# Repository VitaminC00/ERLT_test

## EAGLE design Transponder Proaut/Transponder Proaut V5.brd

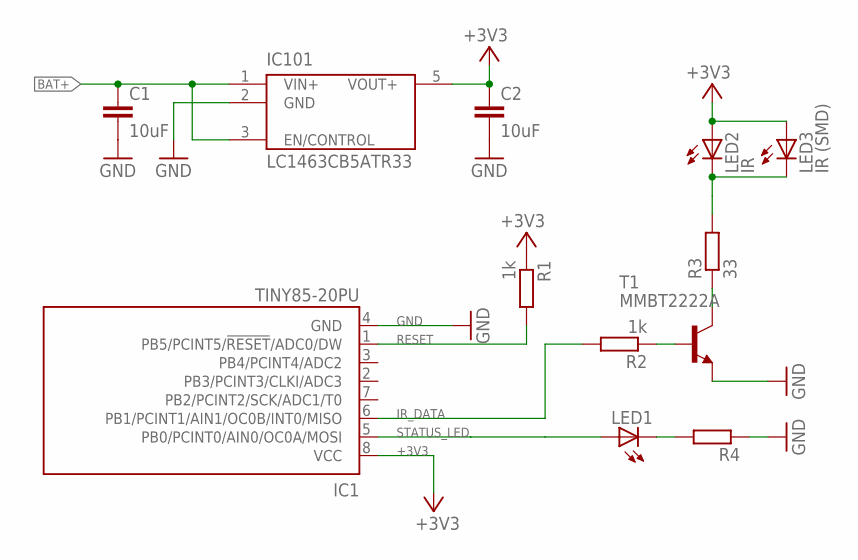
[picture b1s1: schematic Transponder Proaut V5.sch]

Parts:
C1, C2: 10uF; C0805K
IC1: TINY85-20PU; 8S2
IC101: LC1463CB5ATR33; SOT23-5
LED1: LEDCHIPLED_0805; CHIPLED_0805
LED2: IR; LED5MM
LED3: IR (SMD); CHIPLED_0805
R1, R2: 1k; R0805@1
R3: 33; R0805@1
R4: R-EU_R0805; R0805@1
T1: MMBT2222A; SOT23-BEC

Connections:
+3V3: C2.1, IC1.8 (VCC), IC101.5 (VOUT+), LED2.A, LED3.A, R1.1
BAT+: C1.1, IC101.1 (VIN+), IC101.3 (EN/CONTROL)
GND: C1.2, C2.2, IC1.4 (GND), IC101.2 (GND), R4.1, T1.E
IR_DATA: IC1.6 (PB1/PCINT1/AIN1/OC0B/INT0/MISO), R2.2
unnamed: LED2.K (C), LED3.C, R3.2
unnamed: R3.1, T1.C
unnamed: R2.1, T1.B
unnamed: LED1.C, R4.2
RESET: IC1.1 (PB5/PCINT5/!RESET!/ADC0/DW), R1.2
STATUS_LED: IC1.5 (PB0/PCINT0/AIN0/OC0A/MOSI), LED1.A

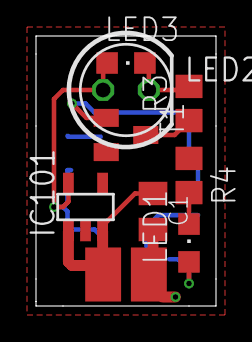
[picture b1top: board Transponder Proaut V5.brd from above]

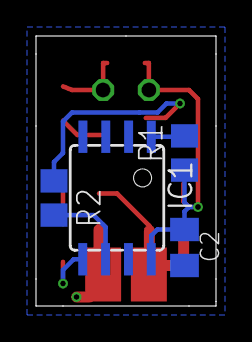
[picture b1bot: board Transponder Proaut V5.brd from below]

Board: 2 copper layers, 10.0 x 15.0 mm, 12 parts (4 on the bottom side), 10 nets.

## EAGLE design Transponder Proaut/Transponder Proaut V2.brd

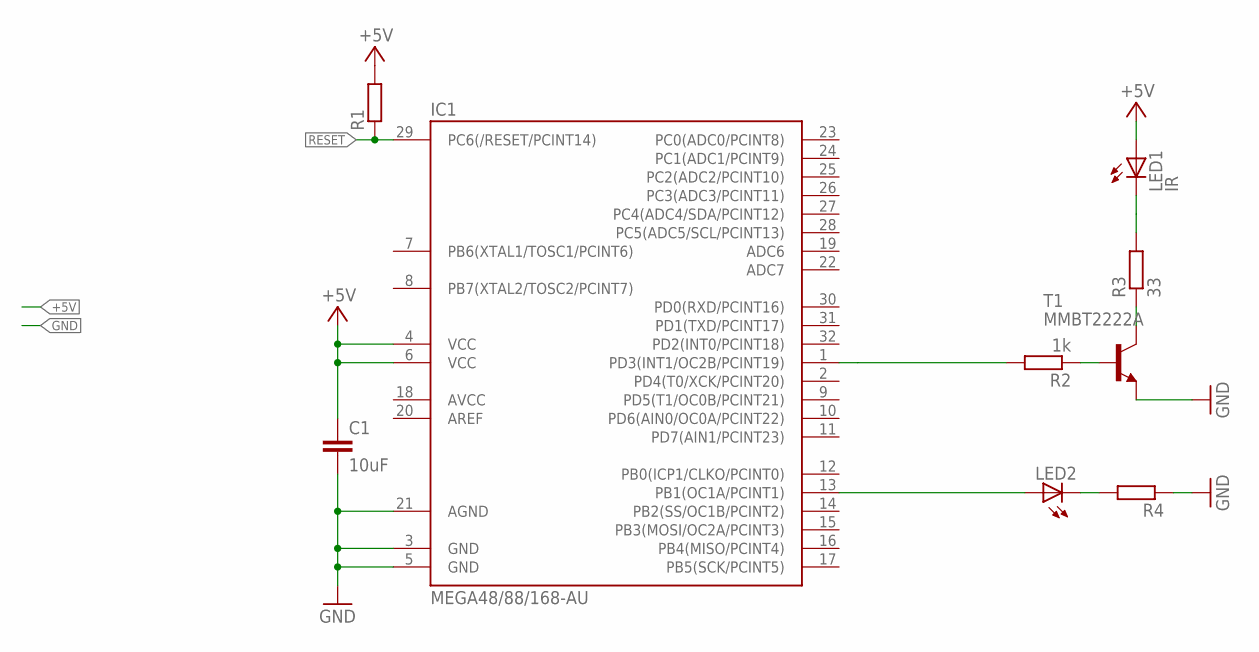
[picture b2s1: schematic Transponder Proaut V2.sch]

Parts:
C1: 10uF; C0805
IC1: MEGA48/88/168-AU; TQFP32-08
LED1: IR; LED5MM
LED2: LEDSML1206; SML1206
R1, R4: R-EU_R0805; R0805@1
R2: 1k; R0805@1
R3: 33; R0805@1
T1: MMBT2222A; SOT23-BEC

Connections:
+5V: C1.1, IC1.4 (VCC), IC1.6 (VCC), LED1.A, R1.2
GND: C1.2, IC1.3 (GND), IC1.5 (GND), IC1.21 (AGND), R4.1, T1.E
IR_LED: IC1.1 (PD3(INT1/OC2B/PCINT19)), R2.2
unnamed: LED1.K (C), R3.2
unnamed: R3.1, T1.C
unnamed: R2.1, T1.B
unnamed: IC1.13 (PB1(OC1A/PCINT1)), LED2.A
unnamed: LED2.C, R4.2
RESET: IC1.29 (PC6(/RESET/PCINT14)), R1.1

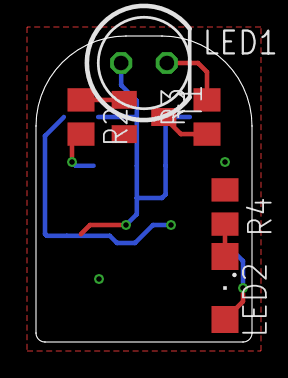
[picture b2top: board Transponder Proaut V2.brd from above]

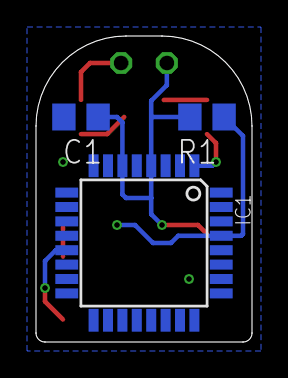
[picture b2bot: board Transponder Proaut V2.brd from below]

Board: 2 copper layers, 12.0 x 17.0 mm, 9 parts (3 on the bottom side), 9 nets.

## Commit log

2017-11-09 added transponder variants
2017-11-09 fix: added missing code line for counting "one_pulses" in "nano_ir_test.ino"
